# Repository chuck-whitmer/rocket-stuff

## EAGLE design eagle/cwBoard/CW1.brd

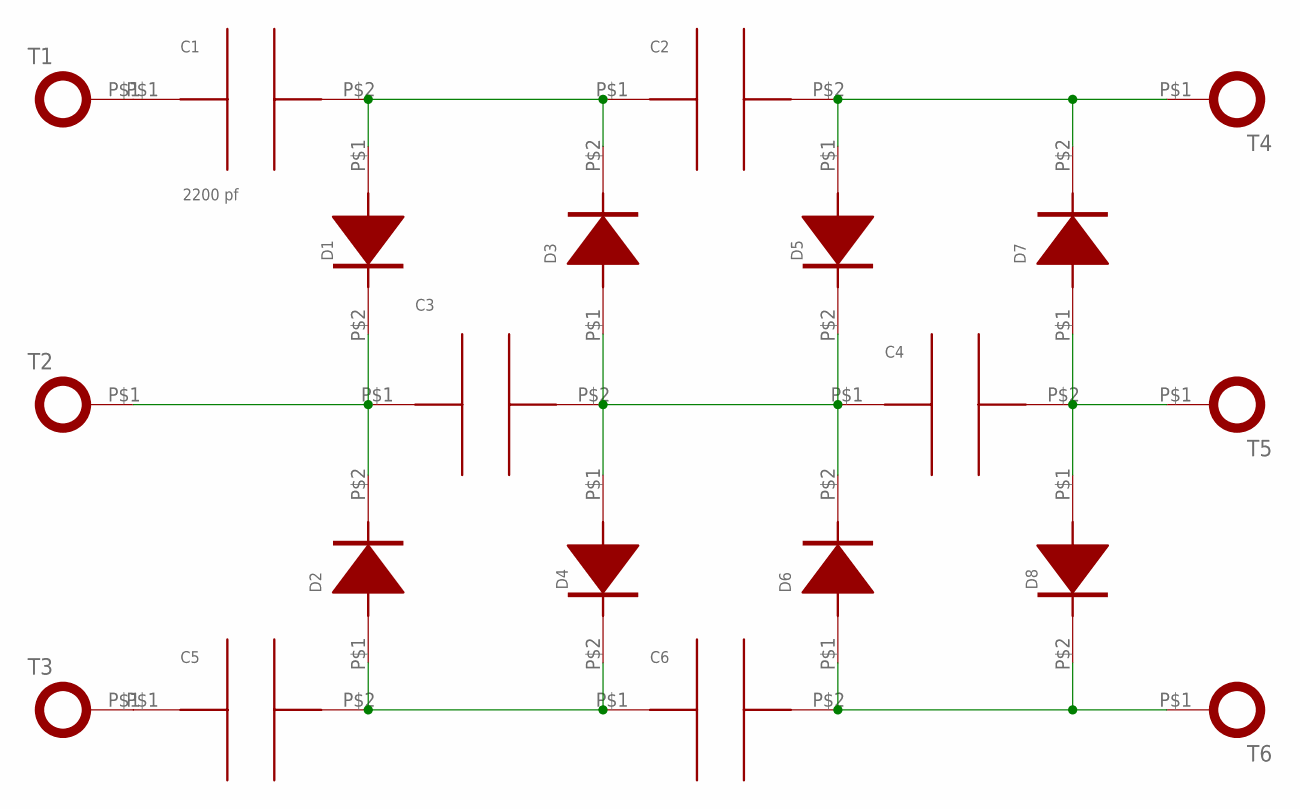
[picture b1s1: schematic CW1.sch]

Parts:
C1: 2200 pf; CAP_CT81_12
C2, C3, C4, C5, C6: HV_CAPACITOR_12MM; CAP_CT81_12
D1, D2, D3, D4, D5, D6, D7, D8: DIODE_14MM; DIODE_14
T1, T2, T3, T4, T5, T6: TERMINAL_M6; LUG_SQUARE_M6

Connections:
unnamed: C1.P$2, C2.P$1, D1.P$1 (ANODE), D3.P$2 (CATHODE)
unnamed: C3.P$1, D1.P$2 (CATHODE), D2.P$2 (CATHODE), T2.P$1
unnamed: C3.P$2, C4.P$1, D3.P$1 (ANODE), D4.P$1 (ANODE), D5.P$2 (CATHODE), D6.P$2 (CATHODE)
unnamed: C5.P$2, C6.P$1, D2.P$1 (ANODE), D4.P$2 (CATHODE)
unnamed: C6.P$2, D6.P$1 (ANODE), D8.P$2 (CATHODE), T6.P$1
unnamed: C4.P$2, D7.P$1 (ANODE), D8.P$1 (ANODE), T5.P$1
unnamed: C1.P$1, T1.P$1
unnamed: C2.P$2, D5.P$1 (ANODE), D7.P$2 (CATHODE), T4.P$1
unnamed: C5.P$1, T3.P$1

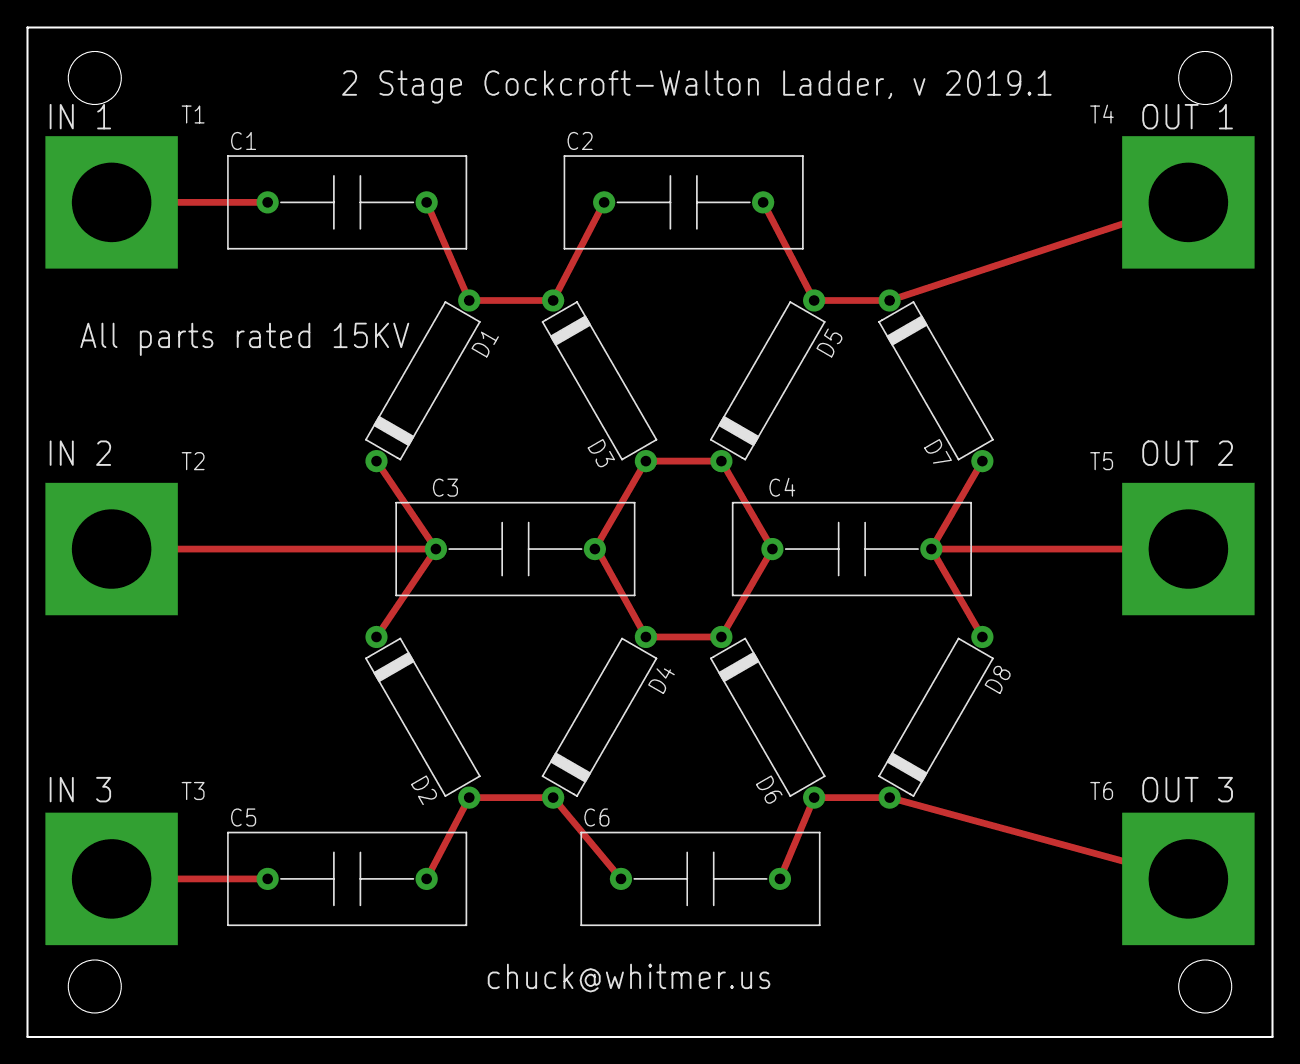
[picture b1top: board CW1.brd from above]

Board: 2 copper layers, 94.0 x 76.2 mm, 20 parts (0 on the bottom side), 9 nets.

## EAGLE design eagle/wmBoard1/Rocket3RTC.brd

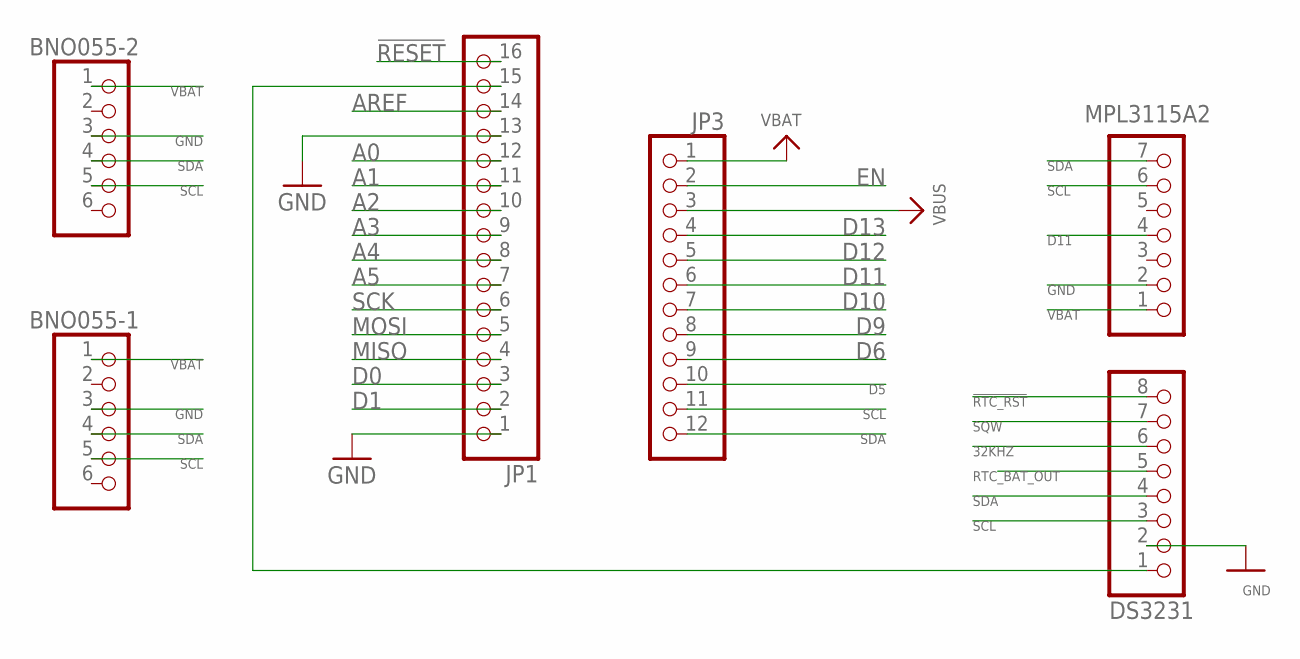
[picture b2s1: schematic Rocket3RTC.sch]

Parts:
BNO055-1, BNO055-2: HEADER-1X670MIL; 1X06_ROUND_70
DS3231: HEADER-1X870MIL; 1X08_ROUND_70
JP1: HEADER-1X16ROUND; 1X16_ROUND
JP3: HEADER-1X12; 1X12_ROUND
MPL3115A2: HEADER-1X770MIL; 1X07_ROUND_70

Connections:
32KHZ: DS3231.6
!RESET: JP1.16
!RTC_RST: DS3231.8
+3V3: DS3231.1, JP1.15
A0: JP1.12
A1: JP1.11
A2: JP1.10
A3: JP1.9
A4: JP1.8
A5: JP1.7
AREF: JP1.14
D0: JP1.3
D1: JP1.2
D5: JP3.10
D6: JP3.9
D9: JP3.8
D10: JP3.7
D11: JP3.6, MPL3115A2.4
D12: JP3.5
D13: JP3.4
EN: JP3.2
GND: BNO055-1.3, BNO055-2.3, DS3231.2, JP1.1, JP1.13, MPL3115A2.2
MISO: JP1.4
MOSI: JP1.5
RTC_BAT_OUT: DS3231.5
SCK: JP1.6
SCL: BNO055-1.5, BNO055-2.5, DS3231.3, JP3.11, MPL3115A2.6
SDA: BNO055-1.4, BNO055-2.4, DS3231.4, JP3.12, MPL3115A2.7
SQW: DS3231.7
VBAT: BNO055-1.1, BNO055-2.1, JP3.1, MPL3115A2.1
VBUS: JP3.3

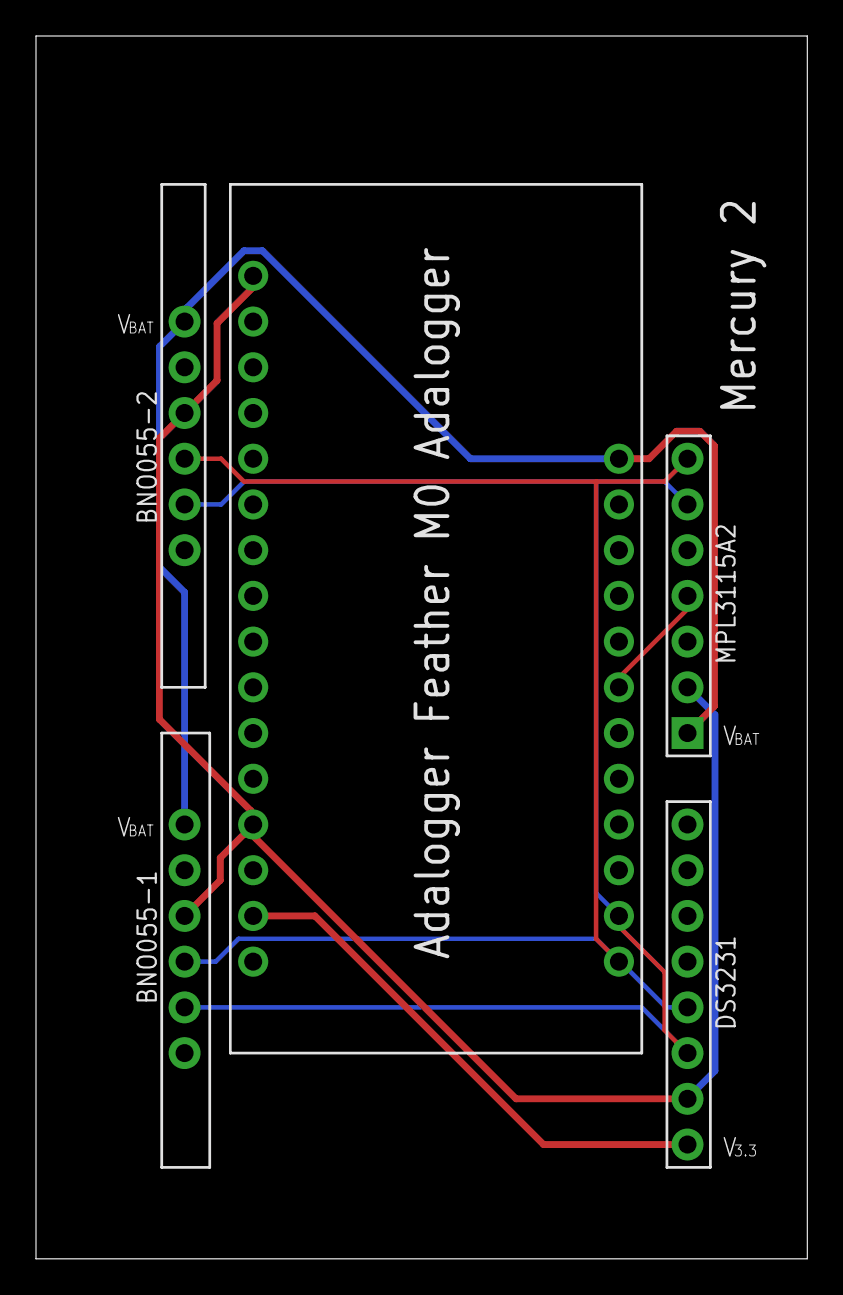
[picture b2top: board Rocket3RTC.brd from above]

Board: 2 copper layers, 42.9 x 67.9 mm, 6 parts (0 on the bottom side), 6 nets.

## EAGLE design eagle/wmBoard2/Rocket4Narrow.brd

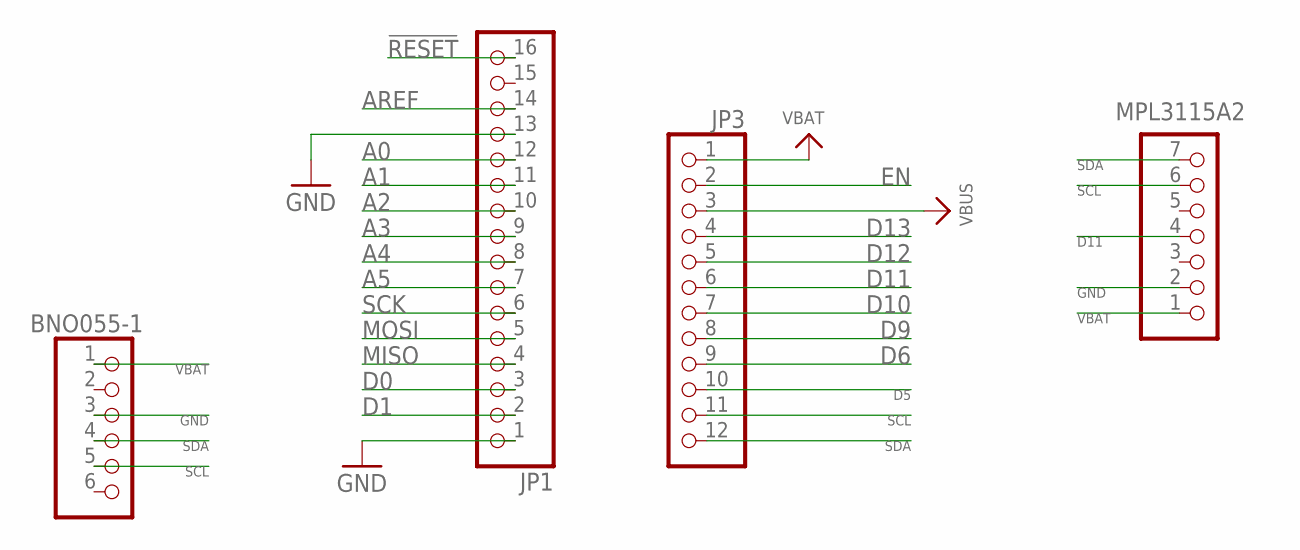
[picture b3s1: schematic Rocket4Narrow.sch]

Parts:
BNO055-1: HEADER-1X670MIL; 1X06_ROUND_70
JP1: HEADER-1X16ROUND; 1X16_ROUND
JP3: HEADER-1X12; 1X12_ROUND
MPL3115A2: HEADER-1X770MIL; 1X07_ROUND_70

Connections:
!RESET: JP1.16
A0: JP1.12
A1: JP1.11
A2: JP1.10
A3: JP1.9
A4: JP1.8
A5: JP1.7
AREF: JP1.14
D0: JP1.3
D1: JP1.2
D5: JP3.10
D6: JP3.9
D9: JP3.8
D10: JP3.7
D11: JP3.6, MPL3115A2.4
D12: JP3.5
D13: JP3.4
EN: JP3.2
GND: BNO055-1.3, JP1.1, JP1.13, MPL3115A2.2
MISO: JP1.4
MOSI: JP1.5
SCK: JP1.6
SCL: BNO055-1.5, JP3.11, MPL3115A2.6
SDA: BNO055-1.4, JP3.12, MPL3115A2.7
VBAT: BNO055-1.1, JP3.1, MPL3115A2.1
VBUS: JP3.3

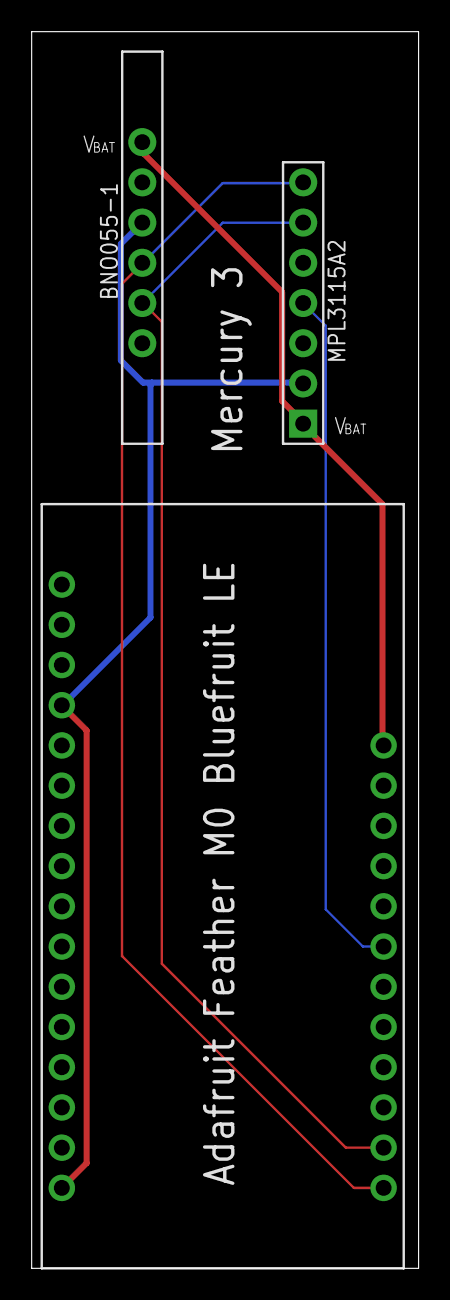
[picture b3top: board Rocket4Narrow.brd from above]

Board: 2 copper layers, 24.4 x 78.1 mm, 4 parts (0 on the bottom side), 5 nets.

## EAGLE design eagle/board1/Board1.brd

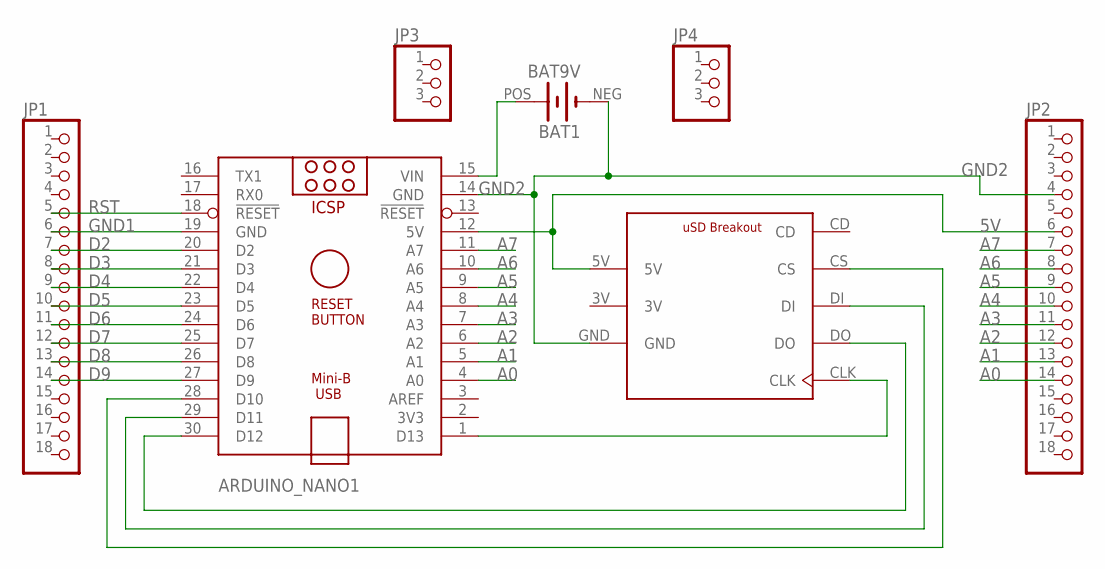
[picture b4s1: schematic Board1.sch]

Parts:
ARDUINO_NANO1: ARDUINO_NANO
BAT1: BAT9V
JP1, JP2: PINHD-1X18; 1X18
JP3, JP4: PINHD-1X3; 1X03
USD1: ADA254

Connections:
5V: ARDUINO_NANO1.12 (5V), JP2.6, USD1.5V
A0: ARDUINO_NANO1.4 (A0), JP2.14
A1: ARDUINO_NANO1.5 (A1), JP2.13
A2: ARDUINO_NANO1.6 (A2), JP2.12
A3: ARDUINO_NANO1.7 (A3), JP2.11
A4: ARDUINO_NANO1.8 (A4), JP2.10
A5: ARDUINO_NANO1.9 (A5), JP2.9
A6: ARDUINO_NANO1.10 (A6), JP2.8
A7: ARDUINO_NANO1.11 (A7), JP2.7
D2: ARDUINO_NANO1.20 (D2), JP1.7
D3: ARDUINO_NANO1.21 (D3), JP1.8
D4: ARDUINO_NANO1.22 (D4), JP1.9
D5: ARDUINO_NANO1.23 (D5), JP1.10
D6: ARDUINO_NANO1.24 (D6), JP1.11
D7: ARDUINO_NANO1.25 (D7), JP1.12
D8: ARDUINO_NANO1.26 (D8), JP1.13
D9: ARDUINO_NANO1.27 (D9), JP1.14
GND1: ARDUINO_NANO1.19 (GND), JP1.6
GND2: ARDUINO_NANO1.14 (GND), BAT1.NEG (-), JP2.4, USD1.GND
unnamed: ARDUINO_NANO1.1 (D13), USD1.CLK
unnamed: ARDUINO_NANO1.30 (D12), USD1.DO
unnamed: ARDUINO_NANO1.29 (D11), USD1.DI
unnamed: ARDUINO_NANO1.28 (D10), USD1.CS
unnamed: ARDUINO_NANO1.15 (VIN), BAT1.POS (+)
RST: ARDUINO_NANO1.18 (!RESET), JP1.5

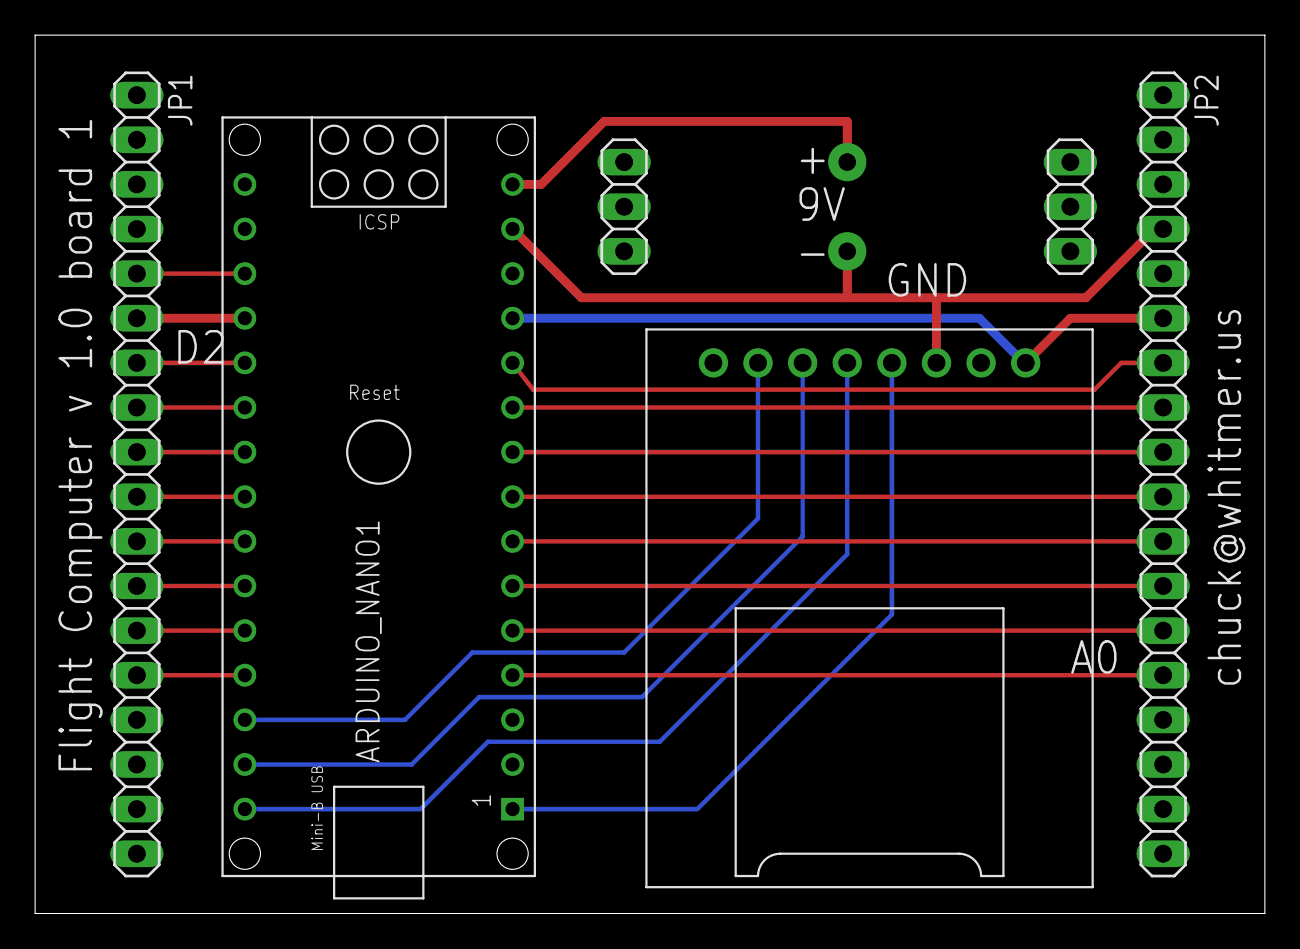
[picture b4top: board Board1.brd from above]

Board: 2 copper layers, 70.0 x 50.0 mm, 7 parts (0 on the bottom side), 25 nets.

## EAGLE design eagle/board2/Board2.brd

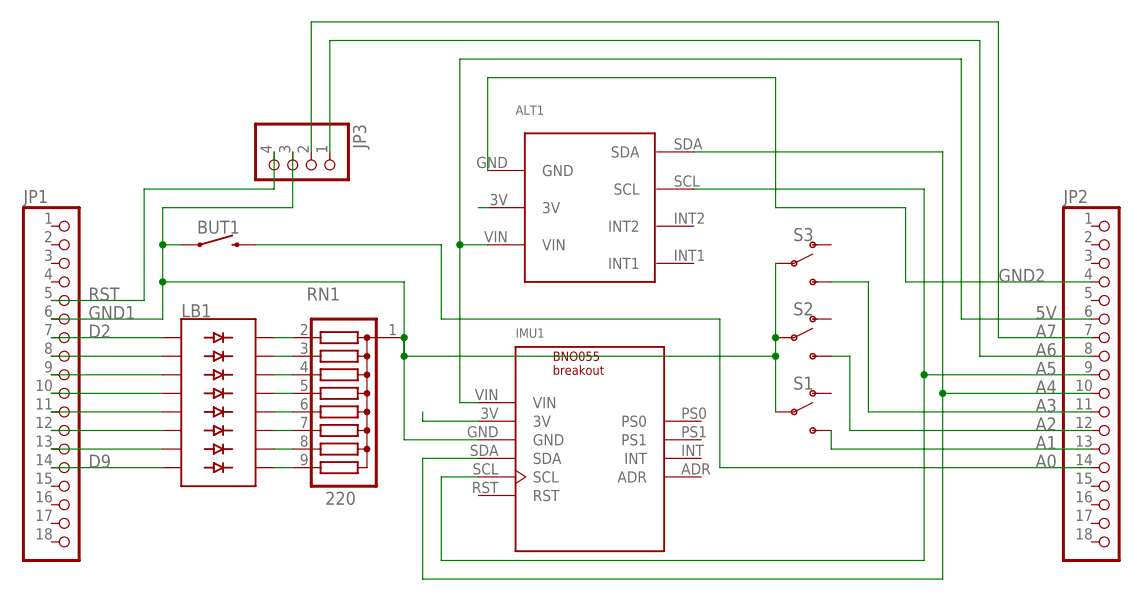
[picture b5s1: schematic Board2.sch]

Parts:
ALT1: ADA1893
BUT1: MOMENTARY-SWITCH-SPST-PTH-6.0MM; TACTILE_SWITCH_PTH_6.0MM
IMU1: ADA2472
JP1, JP2: PINHD-1X18; 1X18
JP3: PINHD-1X4; 1X04
LB1: LB8
RN1: 220; SIL9
S1, S2, S3: SWITCH-SPDT-PTH-11.6X4.0MM; SWITCH_SPDT_PTH_11.6X4.0MM

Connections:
5V: ALT1.VIN, IMU1.VIN, JP2.6
A0: BUT1.3 (2), JP2.14
A1: JP2.13, S1.3 (S)
A2: JP2.12, S2.3 (S)
A3: JP2.11, S3.3 (S)
A4: ALT1.SDA, IMU1.SDA, JP2.10
A5: ALT1.SCL, IMU1.SCL, JP2.9
A6: JP2.8, JP3.1
A7: JP2.7, JP3.2
D2: JP1.7, LB1.1 (A0)
D9: JP1.14, LB1.8 (A7)
GND1: BUT1.1, IMU1.GND, JP1.6, JP3.3, RN1.1, S1.2, S2.2, S3.2
GND2: ALT1.GND, JP2.4
unnamed: JP1.8, LB1.2 (A1)
unnamed: JP1.9, LB1.3 (A2)
unnamed: JP1.10, LB1.4 (A3)
unnamed: JP1.11, LB1.5 (A4)
unnamed: JP1.12, LB1.6 (A5)
unnamed: JP1.13, LB1.7 (A6)
unnamed: LB1.16 (C0), RN1.2
unnamed: LB1.15 (C1), RN1.3
unnamed: LB1.14 (C2), RN1.4
unnamed: LB1.13 (C3), RN1.5
unnamed: LB1.12 (C4), RN1.6
unnamed: LB1.11 (C5), RN1.7
unnamed: LB1.10 (C6), RN1.8
unnamed: LB1.9 (C7), RN1.9
RST: JP1.5, JP3.4

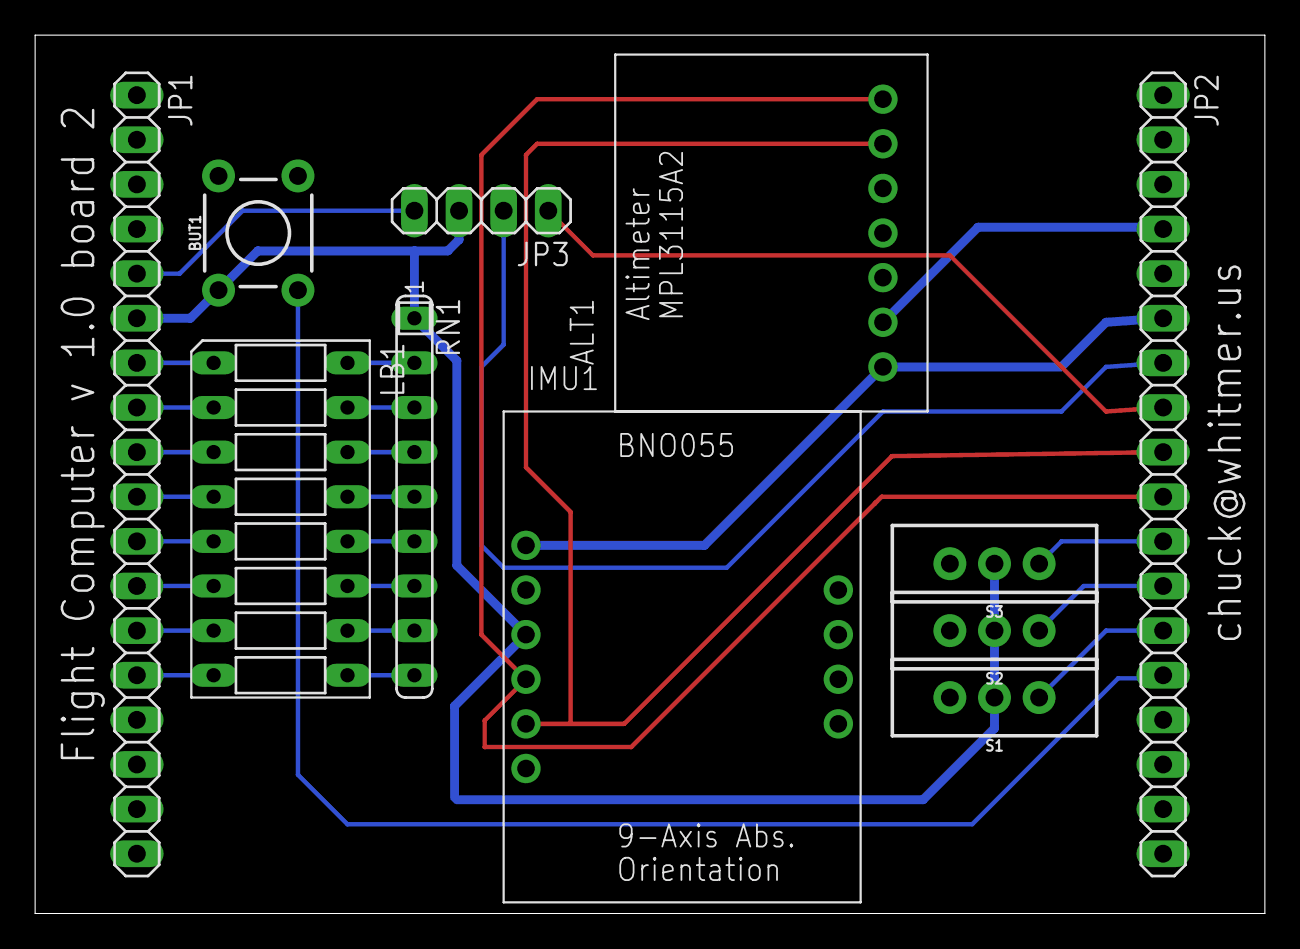
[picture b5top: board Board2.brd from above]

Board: 2 copper layers, 70.0 x 50.0 mm, 11 parts (0 on the bottom side), 28 nets.

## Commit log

2019-03-15 whatever
2019-03-15 Initial add.
2019-03-15 Stop tracking acc calibration status. It's just serial noise for us.
2019-03-15 Can use 8g, but not in fusion mode.
2019-03-20 Added 3D printed rocket parts.
2019-03-21 Added body tube info
2019-03-22 The libraries folder should contain soft links to where the right driver files live.
2019-03-22 Testing the add of a symbolic link
2019-03-25 Compiles with new libraries location
2019-03-26 Updated and running in Issq
2019-03-26 Need to create libraries folder
2019-03-27 First pass at LogRawData
2019-03-28 LogRawData writes binary info at 250 Hz. New ACC data every 8 msec, new GYRO data every 10 msec.
2019-03-31 Two launches yesterday with F15-6. Binary files. Pre-launch weight 496g.
2019-04-01 rocket-code dat to txt converter
2019-04-06 Starting data analysis
2019-04-08 Last logdata changes from laptop
2019-04-11 Added uSD to parts library
2019-04-12 latest pcb stuff
2019-04-12 Added options for reading binary data file. Latest PCB work.
2019-04-12 Board 1 nearly complete
2019-04-14 Board 2 sized and tuned
2019-04-14 Latest mods
2019-04-14 Resize and tune board 1
2019-04-16 Thickened lines, spread switches apart a bit
2019-04-17 Relocate boards to their own folders
2019-04-17 Walter's first two adafruit based boards
2019-04-18 Updated for board routing
2019-04-18 Add RTC part to libraries and to board2
2019-04-20 Added fin slot holder
2019-04-21 Working design with maximum width
2019-04-21 Standard width of 20mm
2019-04-22 Just changed to do BT-80
2019-04-30 Adding Corel file. Keep these in version 16 please.
2019-05-01 rocket-code: Added usage
2019-05-02 Corel: Laser fin cutting
2019-05-06 Updated files during model build
2019-05-09 Start camera mount
2019-05-09 OpenSCAD: Latest part updates
2019-05-09 OpenSCAD: more camera work
2019-05-24 Added HV parts to library
2019-05-27 Cut into top and bottom
2019-05-27 A Cockcroft-Walton board that doesn't belong here
2019-05-29 Moved diode stripe to tPlace
2019-05-29 CW board: Final submitted design
2019-11-15 Added packing list
2019-11-15 Relocate stl files
2019-11-19 Ejection Piston updates
2019-11-20 Added screw holes for M4 mounting

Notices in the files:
parts and their libraries:
SparkFun-Switches: Licensing: Creative Commons ShareAlike 4.0 International - https://creativecommons.org/licenses/by-sa/4.0
microbuilder: This work is placed in the public domain, and may be freely used for commercial and non-commercial work with the following conditions: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
